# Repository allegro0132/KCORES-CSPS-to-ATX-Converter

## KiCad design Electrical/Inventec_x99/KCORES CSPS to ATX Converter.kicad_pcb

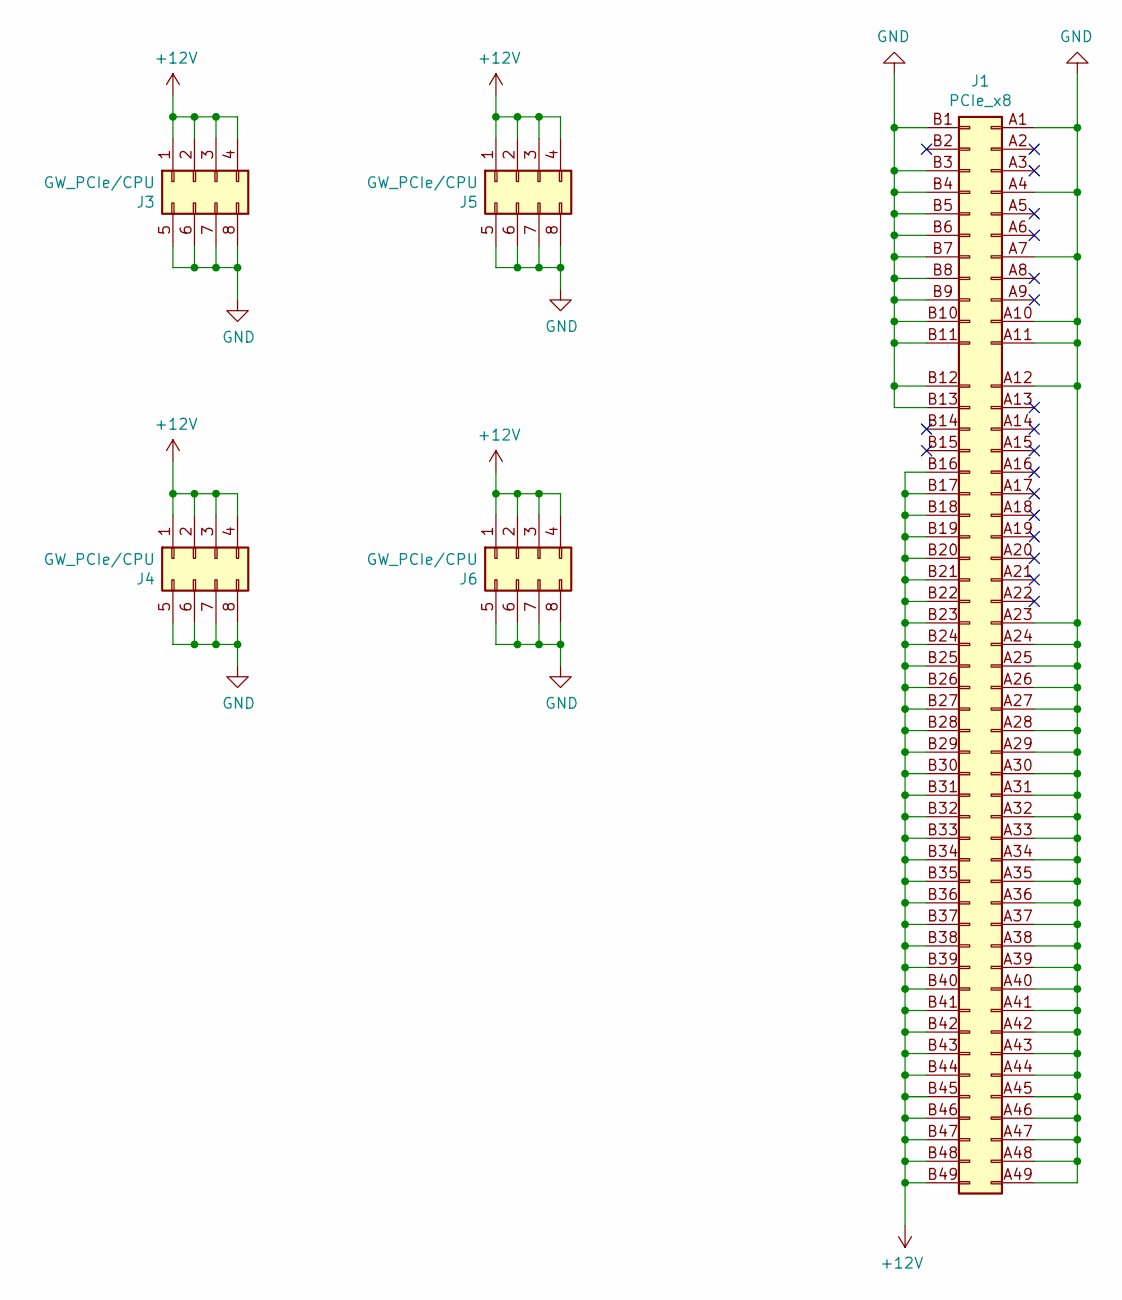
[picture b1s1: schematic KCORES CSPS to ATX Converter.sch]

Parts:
J1: PCIe_x8; BUS_PCIexpress_x8
J3, J4, J5, J6: GW_PCIe/CPU; ATX_8Pin_P4.20mm_Vertical_4.20mm

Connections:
+12V: J1.B16, J1.B17, J1.B18, J1.B19, J1.B20, J1.B21, J1.B22, J1.B23, J1.B24, J1.B25, J1.B26, J1.B27, J1.B28, J1.B29, J1.B30, J1.B31, J1.B32, J1.B33, J1.B34, J1.B35, J1.B36, J1.B37, J1.B38, J1.B39, J1.B40, J1.B41, J1.B42, J1.B43, J1.B44, J1.B45, J1.B46, J1.B47, J1.B48, J1.B49, J3.1, J3.2, J3.3, J3.4, J4.1, J4.2, J4.3, J4.4, J5.1, J5.2, J5.3, J5.4, J6.1, J6.2, J6.3, J6.4
GND: J1.A1, J1.A4, J1.A7, J1.A10, J1.A11, J1.A12, J1.A23, J1.A24, J1.A25, J1.A26, J1.A27, J1.A28, J1.A29, J1.A30, J1.A31, J1.A32, J1.A33, J1.A34, J1.A35, J1.A36, J1.A37, J1.A38, J1.A39, J1.A40, J1.A41, J1.A42, J1.A43, J1.A44, J1.A45, J1.A46, J1.A47, J1.A48, J1.A49, J1.B1, J1.B3, J1.B4, J1.B5, J1.B6, J1.B7, J1.B8, J1.B9, J1.B10, J1.B11, J1.B12, J1.B13, J3.5, J3.6, J3.7, J3.8, J4.5, J4.6, J4.7, J4.8, J5.5, J5.6, J5.7, J5.8, J6.5, J6.6, J6.7, J6.8

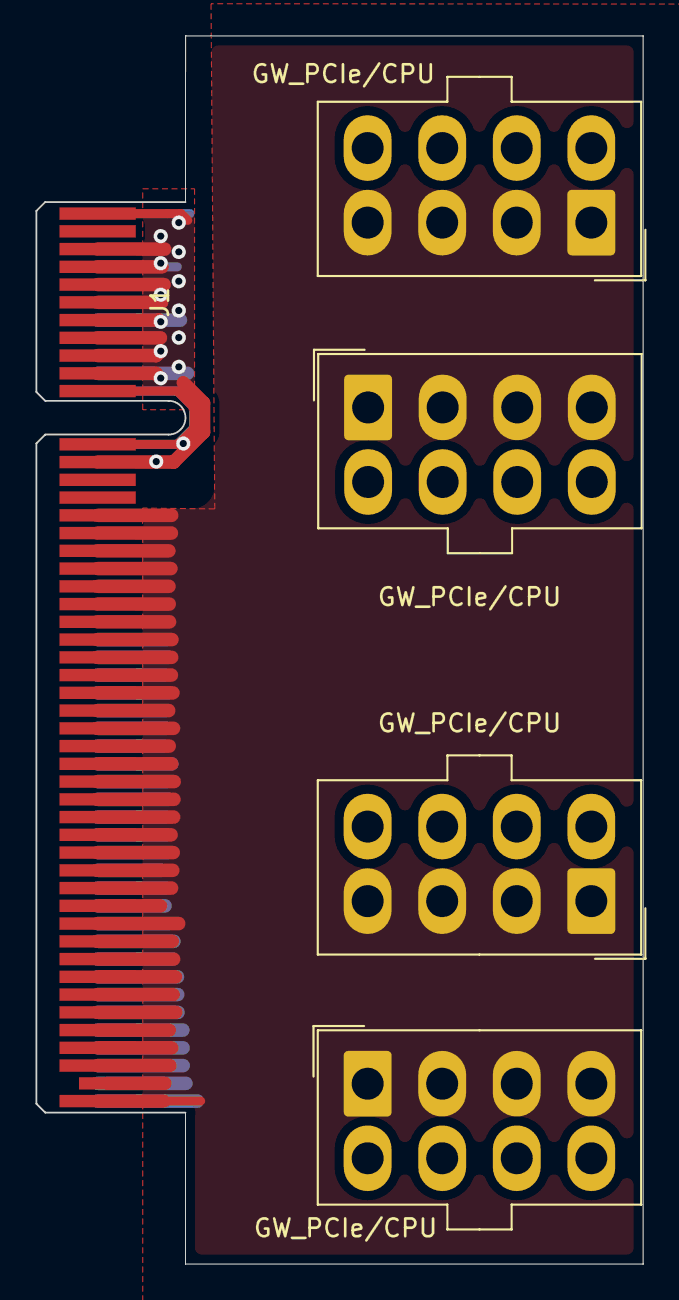
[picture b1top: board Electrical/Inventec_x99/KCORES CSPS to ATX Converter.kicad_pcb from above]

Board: 2 copper layers, 34.2 x 69.1 mm, 5 parts (0 on the bottom side), 2 nets.

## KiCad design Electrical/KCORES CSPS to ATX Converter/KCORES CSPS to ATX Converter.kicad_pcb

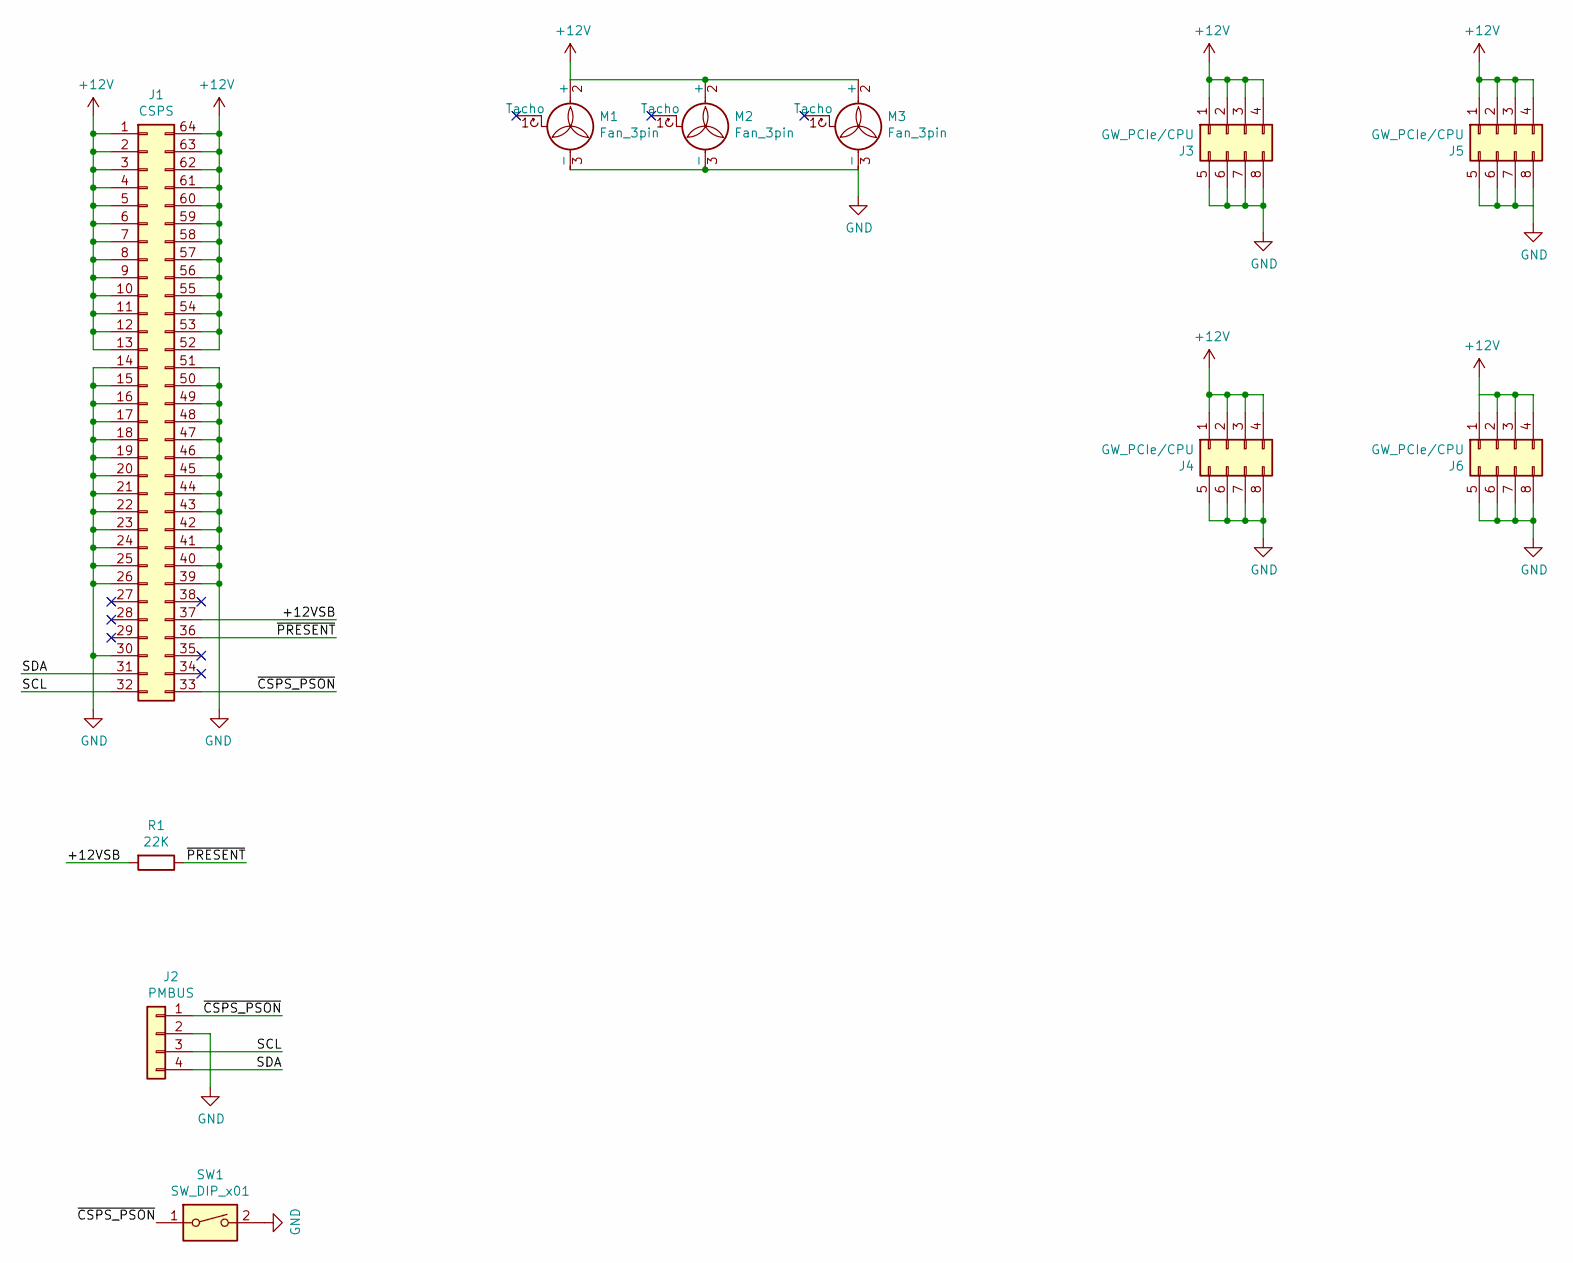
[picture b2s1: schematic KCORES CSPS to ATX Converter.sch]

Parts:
J1: CSPS; CSPS_64P_2.54mm
J2: PMBUS; PinHeader_1x04_P2.54mm_Vertical
J3, J4, J5, J6: GW_PCIe/CPU; ATX_8Pin_P4.20mm_Vertical_4.20mm
M1, M2, M3: Fan_3pin; FanPinHeader_1x03_P2.54mm_Vertical
R1: 22K; R_0603_1608Metric
SW1: SW_DIP_x01; SW_DIP_SPSTx01_Slide_9.78x4.72mm_W7.62mm_P2.54mm

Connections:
+12V: J1.1, J1.2, J1.3, J1.4, J1.5, J1.6, J1.7, J1.8, J1.9, J1.10, J1.11, J1.12, J1.13, J1.52, J1.53, J1.54, J1.55, J1.56, J1.57, J1.58, J1.59, J1.60, J1.61, J1.62, J1.63, J1.64, J3.1, J3.2, J3.3, J3.4, J4.1, J4.2, J4.3, J4.4, J5.1, J5.2, J5.3, J5.4, J6.1, J6.2, J6.3, J6.4, M1.2 (+), M2.2 (+), M3.2 (+); also elsewhere on the board
/+12VSB: J1.37, R1.2
/SCL: J1.32, J2.3
/SDA: J1.31, J2.4
/~CSPS_PSON: J1.33, J2.1, SW1.1
/~PRESENT: J1.36, R1.1
GND: J1.14, J1.15, J1.16, J1.17, J1.18, J1.19, J1.20, J1.21, J1.22, J1.23, J1.24, J1.25, J1.26, J1.30, J1.39, J1.40, J1.41, J1.42, J1.43, J1.44, J1.45, J1.46, J1.47, J1.48, J1.49, J1.50, J1.51, J2.2, J3.5, J3.6, J3.7, J3.8, J4.5, J4.6, J4.7, J4.8, J5.5, J5.6, J5.7, J5.8, J6.5, J6.6, J6.7, J6.8, M1.3 (-), M2.3 (-), M3.3 (-), SW1.2; also elsewhere on the board

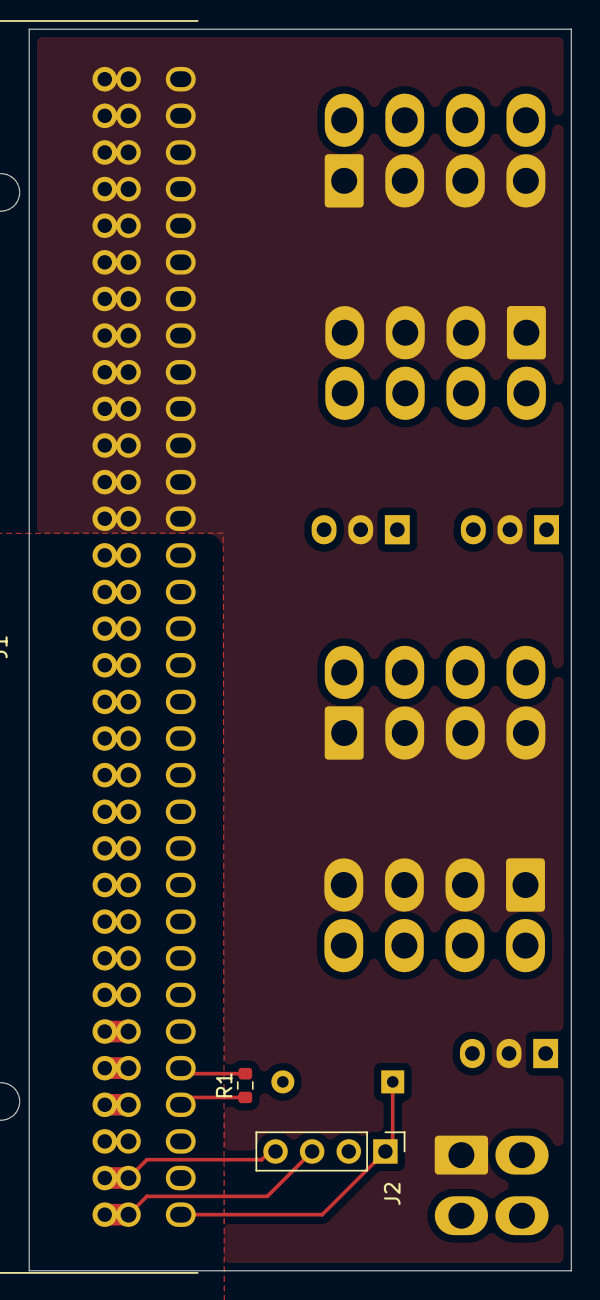
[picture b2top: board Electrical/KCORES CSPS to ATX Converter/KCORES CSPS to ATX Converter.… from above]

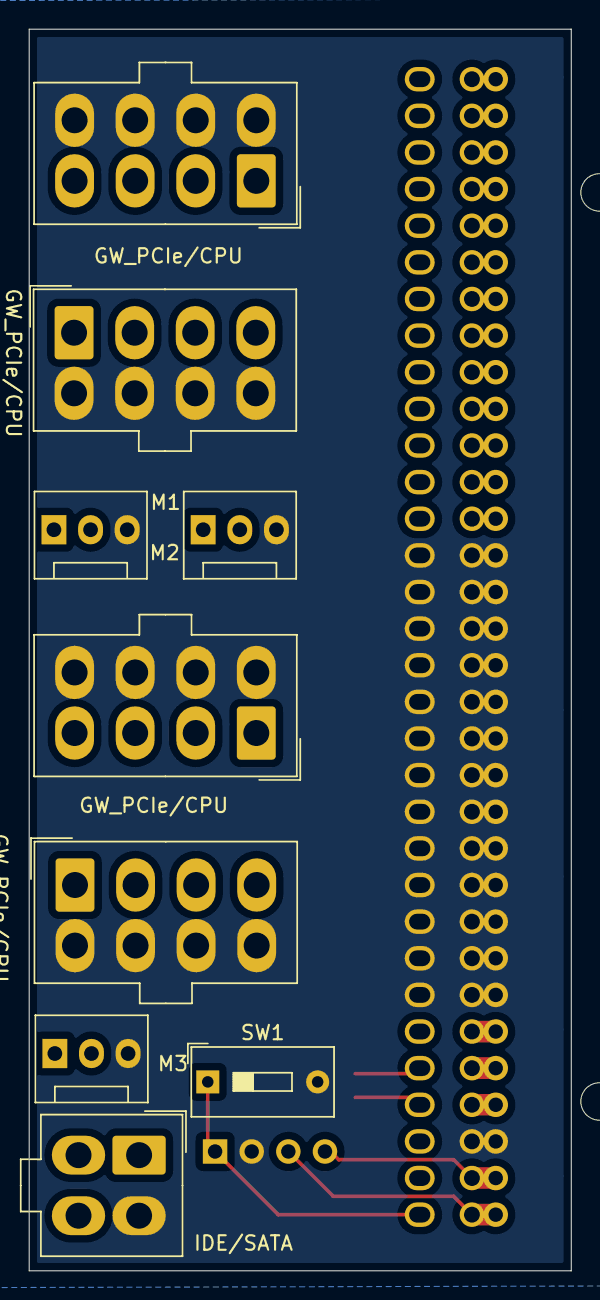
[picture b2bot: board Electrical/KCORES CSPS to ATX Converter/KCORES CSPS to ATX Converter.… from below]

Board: 2 copper layers, 37.6 x 86.1 mm, 12 parts (9 on the bottom side), 7 nets.

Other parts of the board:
J8: IDE/SATA; ATX_4Pin_P4.20mm_Vertical_4.20mm

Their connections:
+12V: J8.1; also elsewhere on the board
GND: J8.2; also elsewhere on the board

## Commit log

2021-05-18 Change modules
    Used PW22 DC to DC modules instead of defaults
2021-05-19 Used SMD Packages
2021-05-22 3d model
2021-09-25 csps part
2021-09-25 v0.1
2021-09-25 v1.0
2021-09-25 release
2021-09-30 ver1.1

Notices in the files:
Electrical/Inventec_x99/KCORES CSPS to ATX Converter.kicad_pcb:
License: KCORES Open Source License
